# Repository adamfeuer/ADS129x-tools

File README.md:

# DEPRECATED

**This repository is deprecated. All software development on these tools is happening elsewhere.** 

**It is recommended you switch to using the successor projects:**

* [HackEEG Arduino driver software](https://github.com/starcat-io/hackeeg-driver-arduino)
* [HackEEG Python client software](https://github.com/starcat-io/hackeeg-client-python)
* [HackEEG shield hardware design files](https://github.com/starcat-io/hackeeg-shield)
* [HackEEG Rust client software](https://github.com/starcat-io/hackeeg-client-rust)

## ADS129x-tools

This is a collection of software for working with the TI ADS129x series of analog to digital
converter chips.

The [TI ADS1299](http://www.ti.com/product/ads1299) is a 24-bit 8-channel ADC meant specifically for EEG, with 24x programmable gain amplifiers and much of the analog circuitry needed for EEG. It is capable of digitizing 16,000 samples per second at 24 bit resolution. The ADS1299-4 is a 4-channel version of the ADS1299; the ADS1299-6 is a 6-channel version.

The [TI ADS1298](http://www.ti.com/product/ads1298) is a 24-bit, 8-channel ADC chip with SPI interface, and 12x programmable gain amplifiers,
meant for ECG and EEG. The ADS1294 is a 4-channel version; ADS1296 is a 6 channel version. 

The ADS1299 and ADS1298 family of chips are ideally suited for digitizing biological signals.

## Arduino drivers

The ads129x-driver/ directory contains an Arduino sketch and associated C/C++ files that make up a driver for ADS129x chips. So far it has only been tested on the ADS1299 and ADS1298, but should work on the other models. This driver has been tested on the Arduino Due and Mega2560, but should also work on other Arduinos. The DMA mode can only be used on the Arduino Due.

The driver has a text-mode interface, so can be used without any client software – just open up a serial port to the SAM3X8E native USB port (line endings NL+CR). It also has a JSONLines mode for easy parsing by client programs and a MessagePack mode for efficient binary communication. 

In MessagePack mode, using the Arduino Due's native SPI DMA, driver can read from the ADS1299 at 16,000 samples per second, and can send that data on to the host via the Arduino Due's USB 2.0 High Speed connection at the same rate. 

By default the driver uses the Arduino library's software SPI (without DMA), and can read and send 8,000 samples per second in that configuration on the Arduino Due, either in JSON Lines mode or MessagePack mode. Other Arduinos will have lower performance.

When in MessagePack mode, MessagePack format is only used to transfer data in `rdata` and `rdatac` commands; all other communication takes place by JSON Lines.

In text mode, samples are encoded using the [base64](http://en.wikipedia.org/wiki/Base64) encoding by default.

## Installing

You must install the [ArduinoJson](https://arduinojson.org/v6/doc/installation/) library before compiling this driver.

## Using the Driver

The commands that are available are:

* RREG – read register. Takes two hex digits as an argument (one byte, for example: FF). Argument 1 is the register to read.
Returns a single hex-encoded byte (for example, 0E) that represents the contents of the register.
* WREG – write register. Takes two hex-encoded bytes as arguments, separated by a space. Argument 1 is the register to write, argument 2 is the register value.
* RDATA – read one sample of data from the ADS129x chip. Returns 3 bytes of header, plus 3 bytes x number of channels (8 for ADS1298 or ADS1299), encoded using base64 or packed hex in text mode, and JSON Lines byte array, or MessagePack byte array, depending on the protocol
* RDATAC – start read data continuous mode. Data is read into a buffer in the Arduino RAM, and streamed to the client one sample at a time, either in packed base64 format or packed hex format in text, JSON Lines byte array, or MessagePack byte array, depending on the protocol.
* SDATAC – stop read data continuous mode. 
* VERSION – reports the driver version
* SERIALNUMBER – reports the HackEEG serial number (UUID from the onboard 24AA256UID-I/SN I2S EEPROM)
* LEDON – turns on the Arduino Due onboard LED.
* LEDOFF – turns off the Arduino Due onboard LED.
* BOARDLEDON – turns on the HackEEG Shield LED. (HackEEG shield has a blue LED connected to ADS1299 GPIO4) 
* BOARDLEDOFF – turns off the HackEEG Shield LED. 
* BASE64 – RDATA/RDATAC commands will encode data in base64.
* TEXT – communication protocol switches to text. See the Communication Protocol section.
* JSONLINES – communication protocol switches from text to [JSONLines](http://jsonlines.org/). This is a text-oriented serialization format with libraries in many languages. See the Communication Protocol section.
* MESSAGEPACK – communication protocol switches from text to [MessagePack](https://msgpack.org) for `rdatac` data only. This is a concise binary serialization format with libraries in many languages. See the Communication Protocol section.
* HEX – RDATA commands will encode data in hexidecimal format.
* HELP – prints a list of available commands.

## General Operation

The ADS129x chips are configured by reading and writing registers. See the chip datasheet for more information about configuring the ADS129x and reading data from it.

If the host program (the program that reads data from the driver) does not pull data from the serial or USB interface fast enough, the driver will block on sending when the serial or USB buffers fill up. This will cause the driver to lose samples. 

The driver uses the Arduino Native port for serial communication, because it is capable of 2 megabits per second or more.

In most applications, the Python 3 usage will go something like this:

```python
#!/usr/bin/env python

SERIAL_PORT_PATH="/dev/cu.usbmodem14434401"  # your actual path to the Arduino Native serial port device goes here
import sys
import hackeeg
from hackeeg import ads1299

hackeeg = hackeeg.HackEEGBoard(SERIAL_PORT_PATH)
hackeeg.connect()
hackeeg.sdatac()
hackeeg.reset()
hackeeg.blink_board_led()
hackeeg.disable_all_channels()
sample_mode = ads1299.HIGH_RES_250_SPS | ads1299.CONFIG1_const
hackeeg.wreg(ads1299.CONFIG1, sample_mode)
test_signal_mode = ads1299.INT_TEST_4HZ | ads1299.CONFIG2_const
hackeeg.wreg(ads1299.CONFIG2, test_signal_mode)
hackeeg.enable_channel(7)
hackeeg.wreg(ads1299.CH7SET, ads1299.TEST_SIGNAL | ads1299.GAIN_1X)
hackeeg.rreg(ads1299.CH5SET)

# Unipolar mode - setting SRB1 bit sends mid-supply voltage to the N inputs
hackeeg.wreg(ads1299.MISC1, ads1299.SRB1)
# add channels into bias generation
hackeeg.wreg(ads1299.BIAS_SENSP, ads1299.BIAS8P)
hackeeg.rdatac()
hackeeg.start()

while True:
    result = hackeeg.read_response()
    status_code = result.get('STATUS_CODE')
    status_text = result.get('STATUS_TEXT')
    data = result.get(hackeeg.DataKey)
    if data:
        decoded_data = result.get(hackeeg.DecodedDataKey)
        if decoded_data:
            timestamp = decoded_data.get('timestamp')
            ads_gpio = decoded_data.get('ads_gpio')
            loff_statp = decoded_data.get('loff_statp')
            loff_statn = decoded_data.get('loff_statn')
            channel_data = decoded_data.get('channel_data')
            print(f"timestamp:{timestamp} | gpio:{ads_gpio} loff_statp:{loff_statp} loff_statn:{loff_statn} |   ",
                  end='')
            for channel_number, sample in enumerate(channel_data):
                print(f"{channel_number + 1}:{sample} ", end='')
            print()
        else:
            print(data)
        sys.stdout.flush()
```

## SPI DMA 

The driver running on the Arduino communicates with the ADS1299 chip via the SPI interface. For data rates from 250 to 8,192 samples per second, the driver can use the Arduino API's built in software SPI. This is simplest.

To use the 16,384 samples per second data rate, or to reduce CPU load on the Arduino Due, the driver can use the Arduino Due's [Atmel SAM3X8E](https://ww1.microchip.com/downloads/en/DeviceDoc/Atmel-11057-32-bit-Cortex-M3-Microcontroller-SAM3X-SAM3A_Datasheet.pdf) CPU's built-in SPI DMA ([Direct Memory Access](https://en.wikipedia.org/wiki/Direct_memory_access)) controller. Using the SPI DMA offloads all SPI communication to the SAM3X8E DMA controller, freeing up the CPU to do other tasks like serial communication. 

To enable this, change the following constants in `SpiDma.cpp` from this:

Arduino software SPI:

```
#define USE_ARDUINO_SPI_LIBRARY 1
#define USE_NATIVE_SAM3X_SPI 0
```

To this (HackEEG SPI DMA):

```
#define USE_ARDUINO_SPI_LIBRARY 0
#define USE_NATIVE_SAM3X_SPI 1
```

Then recompile and upload the driver sketch to the Arduino.

## Communication Protocol

### Text mode

The driver starts up in this mode. This mode is easiest to use when quick communication with the board is needed without a client program. 

When the command TEXT is given, the driver communication protocol switches to text, and the response will be in text format. Commands can be given in lower or upper case, parameters separated by a space. Responses are given on one line, starting with a status code (200 for OK, errors are in the 300s and 400s.) Commands can be given in upper or lower case.

### JSON Lines mode

Give the JSONLINES command to switch to this mode.

When the command JSONLINES is given, the driver communication protocol switches to [JSON Lines](http://jsonlines.org/) format, and the response will be in JSON Lines format. Commands and Responses are a single map, with keys and values determine the command and parameters. The format is as follows (on separate lines for readability; in use, the entire JSON blob would be on its own line):

#### Commands:

```
{
    COMMAND: "<command-name>",
    PARAMETERS: [ <param1>, <param2>, ... ]
}
```

#### Responses:

```
{
    STATUS_CODE: <status-code>,
    STATUS_TEXT: "<status-text>",
    HEADERS: ["header1", "header2", ... ],
    DATA: [value1, value2, value3, ... ]
}
```

Here is an example exchange:

```
{"COMMAND" : "boardledon"}
{"STATUS_CODE" : 200, "STATUS_TEXT": "Ok" }

```

Headers are optional and may or may not be provided.

#### JSON Lines concise mode for `rdata` and `rdatc` responses

For `rdata` and `rdatac` responses, in order to send data at high speeds, a special response format is used that is similar to the MessagePack format:

```
{
    C: <status-code>,
    D: "<base64-encoded byte-array>"
}
```

In concise JSON Lines mode, status text is omitted. The data is sent as a base64-encoded byte array to minimize transformation of the data into human-readable form. This allows faster transfer. See below for the format of the decoded data byte-array.

#### Software library

The Arduino driver uses the [ArduinoJson](https://arduinojson.org/) library for encoding and decoding JSON Lines data, except for `rdata` and `rdatac` messages– those use a custom, optimized sending routine.

### MessagePack mode

Give the MESSAGEPACK command to switch to this mode.

When the command MESSAGEPACK is given, the driver communication protocol for `rdata` and `rdatac` data packets ONLY switches to [MessagePack](https://msgpack.org) concise binary format. Commands are still given in JSON Lines format, and responses for all commands other than `rdata` and `rdatac` will be in JSON Lines. Responses for `rdata` and `rdatac` will be in MessagePack format. This mode is available to improve data transfer speed since the binary data from the SPI interface can be transferred as-is with no copying or transformation.

The format is as follows (on separate lines as JSON for readability, in use this would be packed as a binary structure):

#### Responses:

```
{
    C: <status-code>,
    D: <byte-array>
}
```

In MessagePack mode, status text is omitted.

#### Software library

The Arduino driver uses the [ArduinoJson](https://arduinojson.org/) library for encoding and decoding MessagePack data, except for `rdata` and `rdatac` messages– those use a custom, optimized sending routine.

### Byte-array Format

The packed byte-array used for `rdata` and `rdatac` transfers has this format:

| position | function      | byte |
|----------|---------------|------|
| 00       | timestamp     |    0 |
| 01       | timestamp     |    1 |
| 02       | timestamp     |    2 |
| 03       | timestamp     |    3 |
| 04       | sample number |    0 |
| 05       | sample number |    1 |
| 06       | sample number |    2 |
| 07       | sample number |    3 |
| 08       | channel 1     |    0 |
| 09       | channel 1     |    1 |
| 10       | channel 1     |    2 |
| 11       | channel 2     |    0 |
| 12       | channel 2     |    1 |
| 13       | channel 2     |    2 |
| 14       | channel 3     |    0 |
| 15       | channel 3     |    1 |
| 16       | channel 3     |    2 |
| 17       | channel 4     |    0 |
| 18       | channel 4     |    1 |
| 19       | channel 4     |    2 |
| 20       | channel 5     |    0 |
| 21       | channel 5     |    1 |
| 22       | channel 5     |    2 |
| 23       | channel 6     |    0 |
| 24       | channel 6     |    1 |
| 25       | channel 6     |    2 |
| 26       | channel 7     |    0 |
| 27       | channel 7     |    1 |
| 28       | channel 7     |    2 |
| 29       | channel 8     |    0 |
| 30       | channel 8     |    1 |
| 31       | channel 8     |    2 |

* `timestamp` is an unsigned long, the result of calling the Arduino's `micros()` function right before the sample is taken.
* `sample number` is an unsigned long, the value is incremented for every sample received by the driver. It is reset every time you issue the `start` command. You can analyze the sample number sequence on the client to see if your client code is dropping or missing samples.
* For an example Python decoding function, see [`_decode_data()`](https://github.com/adamfeuer/ADS129x-tools/blob/master/ads129x_client/hackeeg/driver.py#L123-L152) in the file `hackeeg/driver.py`.

## Python Client Software

The Python client software is designed to run on a laptop computer. There is a `hackeeg` driver Python module for communicating with the Arduino over the USB serial port, a command line client (`hackeeg_shell` wrapper and `hackeeg_shell.py` Python client), and a demonstration and performance testing script (`hackeeg_test.py`). 

The `hackeeg_shell.py` and `hackeeg_test.py` programs set the Arduino driver to JSON Lines mode, and communicate with it that way. They issue JSON Lines commands to the Arduino, and recieve JSON Lines or MessagePack data in response.

Using Python 3.6.5 on a 2017 Retina Macbook Pro, connected to an Arduino Due configured to use the SPI DMA included in the driver, and using the MessagePack mode, the `hackeeg_test.py` program can read and transfer 8 channels of 24-bit resolution data at 16,384 samples per second, the maximum rate of the ADS1299 chip.

The Python client software requires the [PySerial](https://github.com/pyserial/pyserial) module.

## Hardware

If you are looking for a full Arduino shield with analog input capability, you might
be interested in the [HackEEG Shield](https://github.com/adamfeuer/hackeeg-shield).
The HackEEG shield is designed for use with the ADS1299.

For prototyping software, the [ADS1298 breakout board](https://github.com/adamfeuer/ADS1298-breakout) might be useful. It is designed for the ADS1298, but should also work with the ADS1294, ADS1296, or ADS1299.

## Credits

This software would not be possible without the help of many people:

* Kendrick Shaw, Ace Medlock, and Eric Herman (parts of the ADS129x.h header file and some parts of the ADS129x driver, see [OpenHardwareExG project](https://github.com/OpenElectronicsLab/OpenHardwareExG) for more info.
* Chris Rorden (some parts of the ADS1298 driver)
* Stefan Rado (SerialCommand library)
* Steven Cogswell (SerialCommand library)
* William Greiman (SPI DMA library)
* Cristian Maglie (SPI DMA library)
* Bill Porter (SPI DMA library)
* Adam Rudd ([Base64](https://github.com/adamvr/arduino-base64) library)
* Benoît Blanchon ([ArduinoJson](https://arduinojson.org/) library)

If I forgot to credit you, please let me know!

If you have questions, comments, or improvements, I would love to know them! Pull requests welcome!

cheers <br/>
adam <br/>
<br/>
Adam Feuer <br/>
adam@starcat.io<br/>
[Starcat LLC](https://starcat.io)<br/>
Seattle, WA, USA <br/>

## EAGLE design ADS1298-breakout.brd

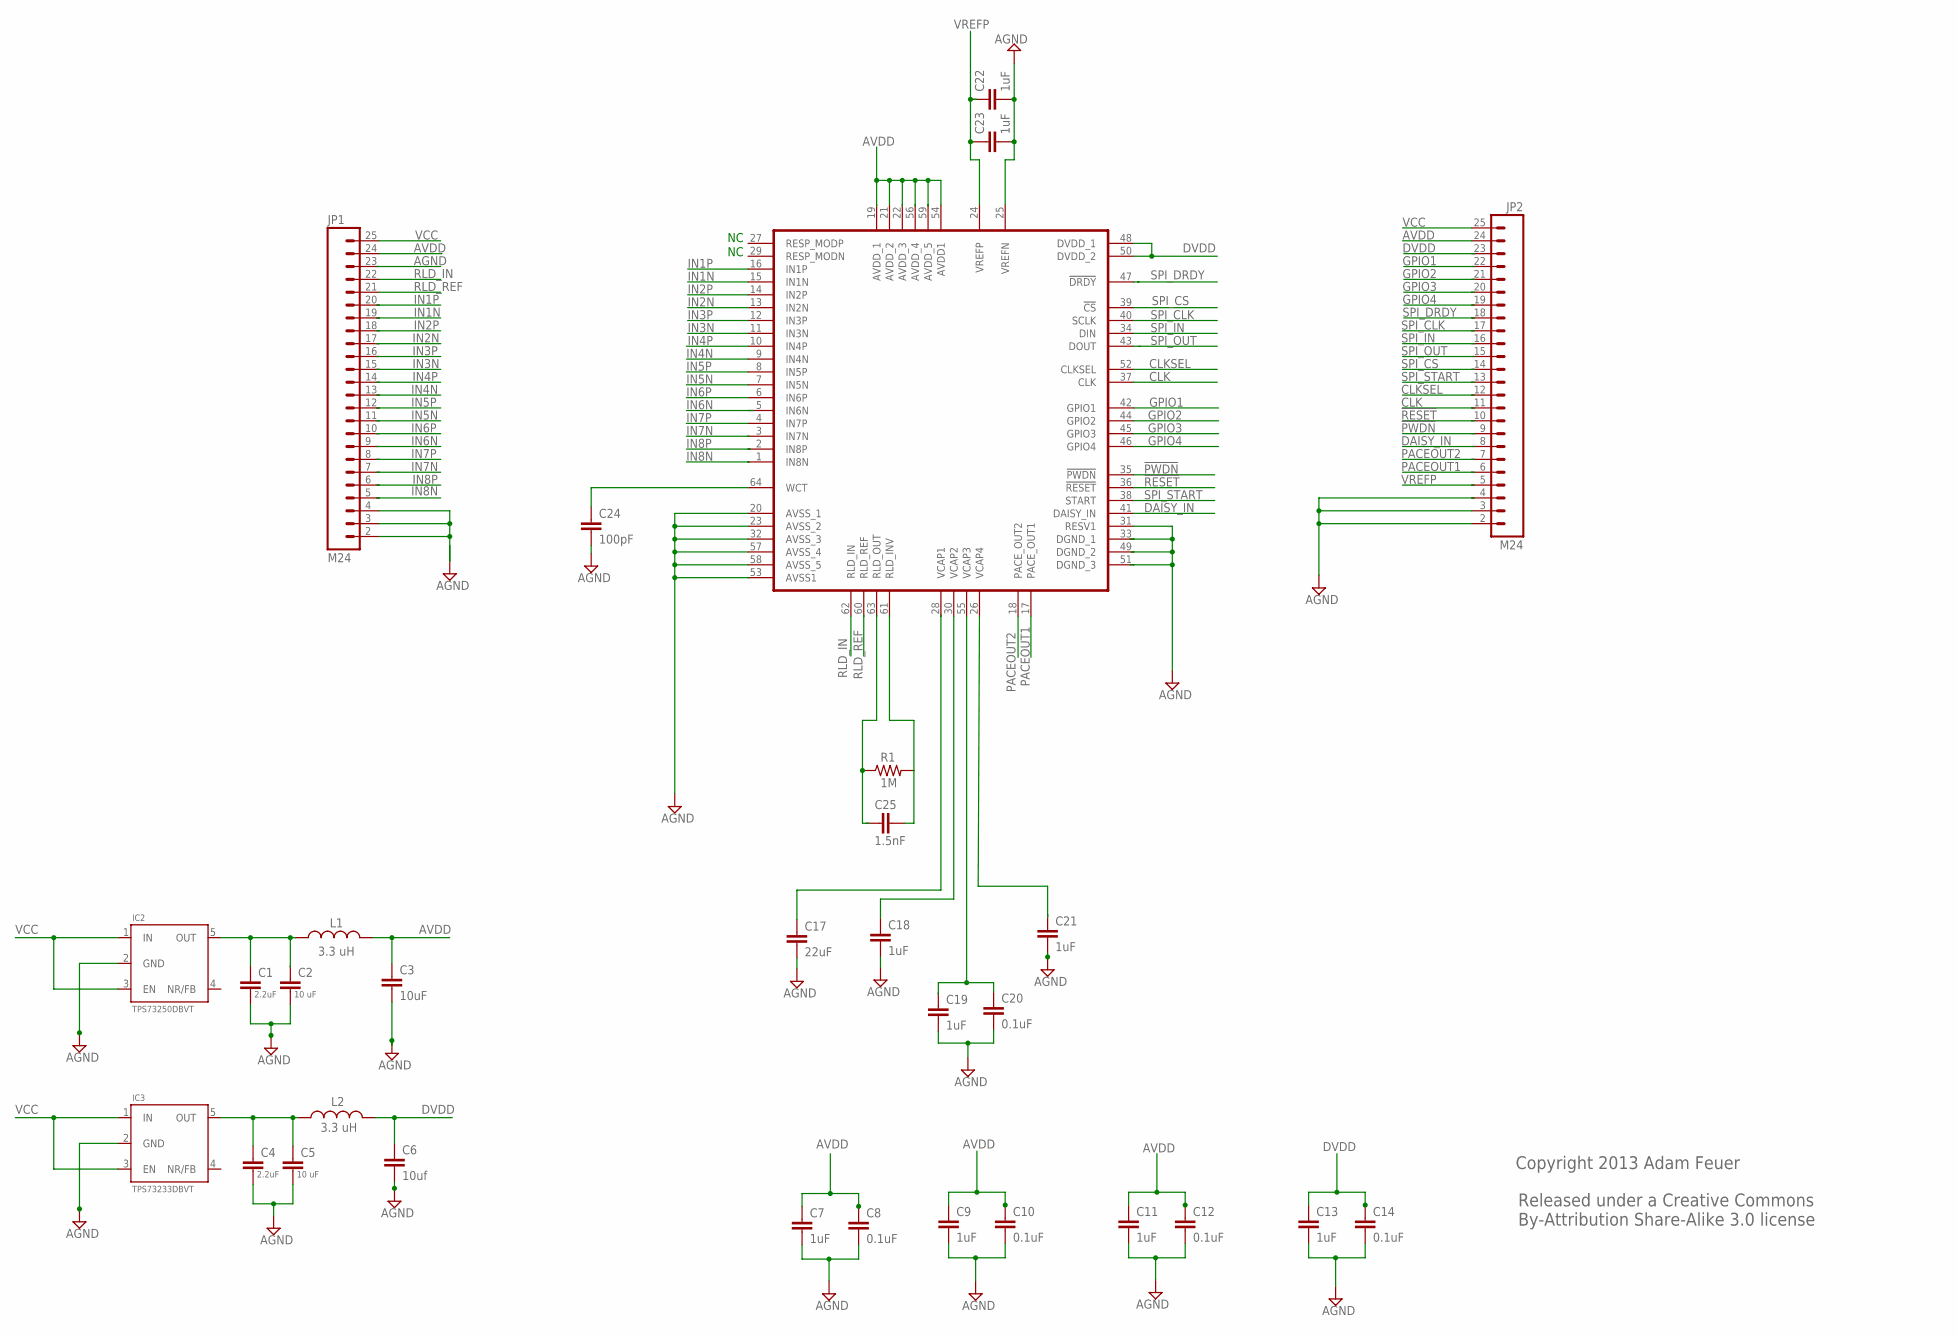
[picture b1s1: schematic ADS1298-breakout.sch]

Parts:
C1, C4: 2.2uF; 0603-CAP
C2, C5: 10 uF; 0603-CAP
C3: 10uF; 0603-CAP
C6: 10uf; 0603-CAP
C7, C9, C11, C13, C18, C19, C21, C22, C23: 1uF; 0603-CAP
C8, C10, C12, C14, C20: 0.1uF; 0603-CAP
C17: 22uF; 0603-CAP
C24: 100pF; 0603-CAP
C25: 1.5nF; 0603-CAP
IC1: ADS1298*PAG*; TQFP64
IC2: TPS73250DBVT; SOT23-5
IC3: TPS73233DBVT; SOT23-5
JP1, JP2: M24; 1X24
L1, L2: 3.3 uH; 0603
R1: 1M; 0603-RES

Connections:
!PWDN: IC1.35 (!PWDN), JP2.9
!RESET: IC1.36 (!RESET), JP2.10
AGND: C1.2, C2.2, C3.2, C4.2, C5.2, C6.2, C7.2, C8.2, C9.2, C10.2, C11.2, C12.2, C13.2, C14.2, C17.2, C18.2, C19.2, C20.2, C21.2, C22.2, C23.2, C24.2, IC1.20 (AVSS_1), IC1.23 (AVSS_2), IC1.25 (VREFN), IC1.31 (RESV1), IC1.32 (AVSS_3), IC1.33 (DGND_1), IC1.49 (DGND_2), IC1.51 (DGND_3), IC1.53 (AVSS1), IC1.57 (AVSS_4), IC1.58 (AVSS_5), IC2.2 (GND), IC3.2 (GND), JP1.2, JP1.3, JP1.4, JP1.23, JP2.2, JP2.3, JP2.4
AVDD: C3.1, C7.1, C8.1, C9.1, C10.1, C11.1, C12.1, IC1.19 (AVDD_1), IC1.21 (AVDD_2), IC1.22 (AVDD_3), IC1.54 (AVDD1), IC1.56 (AVDD_4), IC1.59 (AVDD_5), JP1.24, JP2.24, L1.2
CLK: IC1.37 (CLK), JP2.11
CLKSEL: IC1.52 (CLKSEL), JP2.12
DAISY_IN: IC1.41 (DAISY_IN), JP2.8
DVDD: C6.1, C13.1, C14.1, IC1.48 (DVDD_1), IC1.50 (DVDD_2), JP2.23, L2.2
GPIO1: IC1.42 (GPIO1), JP2.22
GPIO2: IC1.44 (GPIO2), JP2.21
GPIO3: IC1.45 (GPIO3), JP2.20
GPIO4: IC1.46 (GPIO4), JP2.19
IN1N: IC1.15 (IN1N), JP1.19
IN1P: IC1.16 (IN1P), JP1.20
IN2N: IC1.13 (IN2N), JP1.17
IN2P: IC1.14 (IN2P), JP1.18
IN3N: IC1.11 (IN3N), JP1.15
IN3P: IC1.12 (IN3P), JP1.16
IN4N: IC1.9 (IN4N), JP1.13
IN4P: IC1.10 (IN4P), JP1.14
IN5N: IC1.7 (IN5N), JP1.11
IN5P: IC1.8 (IN5P), JP1.12
IN6N: IC1.5 (IN6N), JP1.9
IN6P: IC1.6 (IN6P), JP1.10
IN7N: IC1.3 (IN7N), JP1.7
IN7P: IC1.4 (IN7P), JP1.8
IN8N: IC1.1 (IN8N), JP1.5
IN8P: IC1.2 (IN8P), JP1.6
unnamed: C4.1, C5.1, IC3.5 (OUT), L2.1
unnamed: C1.1, C2.1, IC2.5 (OUT), L1.1
unnamed: C17.1, IC1.28 (VCAP1)
unnamed: C18.1, IC1.30 (VCAP2)
unnamed: C19.1, C20.1, IC1.55 (VCAP3)
unnamed: C24.1, IC1.64 (WCT)
unnamed: C21.1, IC1.26 (VCAP4)
PACEOUT1: IC1.17 (PACE_OUT1), JP2.6
PACEOUT2: IC1.18 (PACE_OUT2), JP2.7
RLD_IN: IC1.62 (RLD_IN), JP1.22
RLD_INV: C25.2, IC1.61 (RLD_INV), R1.2
RLD_OUT: C25.1, IC1.63 (RLD_OUT), R1.1
RLD_REF: IC1.60 (RLD_REF), JP1.21
SPI_CLK: IC1.40 (SCLK), JP2.17
SPI_CS: IC1.39 (!CS), JP2.14
SPI_DRDY: IC1.47 (!DRDY), JP2.18
SPI_IN: IC1.34 (DIN), JP2.16
SPI_OUT: IC1.43 (DOUT), JP2.15
SPI_START: IC1.38 (START), JP2.13
VCC: IC2.1 (IN), IC2.3 (EN), IC3.1 (IN), IC3.3 (EN), JP1.25, JP2.25
VREFP: C22.1, C23.1, IC1.24 (VREFP), JP2.5

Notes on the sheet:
Released under a Creative Commons By-Attribution Share-Alike 3.0 license
Copyright 2013 Adam Feuer

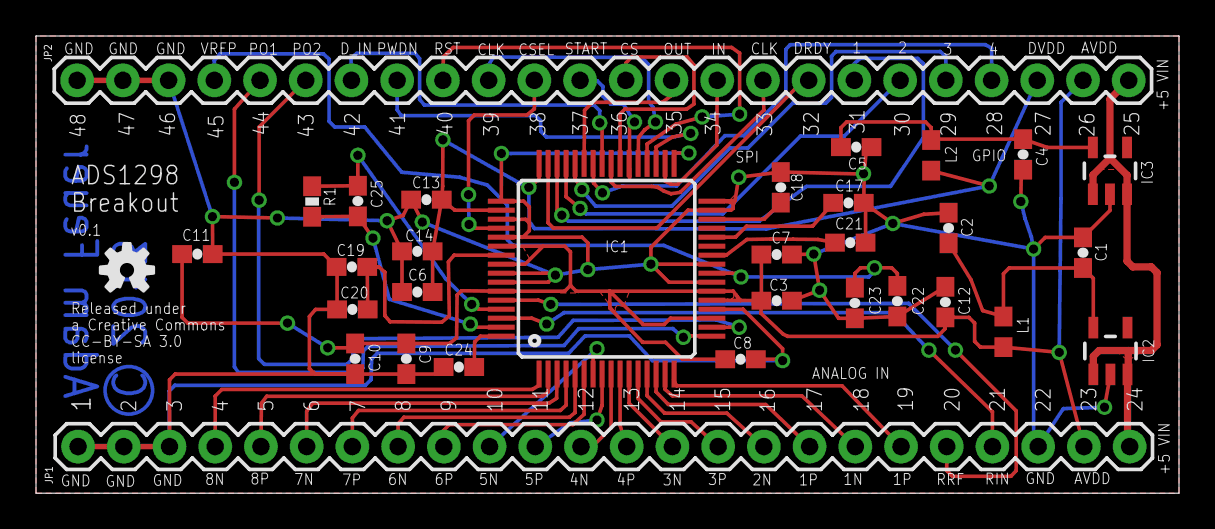
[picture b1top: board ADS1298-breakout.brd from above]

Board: 2 copper layers, 63.5 x 25.4 mm, 32 parts (0 on the bottom side), 49 nets.

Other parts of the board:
U$1: OSHW-LOGO-S

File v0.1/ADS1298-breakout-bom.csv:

"Part";"Value";"Device";"Package";"Description";"";
"C1";"2.2uF";"CAP0603-CAP";"0603-CAP";"Capacitor";"";
"C2";"10 uF";"CAP0603-CAP";"0603-CAP";"Capacitor";"";
"C3";"10uF";"CAP0603-CAP";"0603-CAP";"Capacitor";"";
"C4";"2.2uF";"CAP0603-CAP";"0603-CAP";"Capacitor";"";
"C5";"10 uF";"CAP0603-CAP";"0603-CAP";"Capacitor";"";
"C6";"10uf";"CAP0603-CAP";"0603-CAP";"Capacitor";"";
"C7";"1uF";"CAP0603-CAP";"0603-CAP";"Capacitor";"";
"C8";"0.1uF";"CAP0603-CAP";"0603-CAP";"Capacitor";"";
"C9";"1uF";"CAP0603-CAP";"0603-CAP";"Capacitor";"";
"C10";"0.1uF";"CAP0603-CAP";"0603-CAP";"Capacitor";"";
"C11";"1uF";"CAP0603-CAP";"0603-CAP";"Capacitor";"";
"C12";"0.1uF";"CAP0603-CAP";"0603-CAP";"Capacitor";"";
"C13";"1uF";"CAP0603-CAP";"0603-CAP";"Capacitor";"";
"C14";"0.1uF";"CAP0603-CAP";"0603-CAP";"Capacitor";"";
"C17";"22uF";"CAP0603-CAP";"0603-CAP";"Capacitor";"";
"C18";"1uF";"CAP0603-CAP";"0603-CAP";"Capacitor";"";
"C19";"1uF";"CAP0603-CAP";"0603-CAP";"Capacitor";"";
"C20";"0.1uF";"CAP0603-CAP";"0603-CAP";"Capacitor";"";
"C21";"1uF";"CAP0603-CAP";"0603-CAP";"Capacitor";"";
"C22";"1uF";"CAP0603-CAP";"0603-CAP";"Capacitor";"";
"C23";"1uF";"CAP0603-CAP";"0603-CAP";"Capacitor";"";
"C24";"100pF";"CAP0603-CAP";"0603-CAP";"Capacitor";"";
"C25";"1.5nF";"CAP0603-CAP";"0603-CAP";"Capacitor";"";
"IC1";"ADS1298*PAG*";"ADS1298*PAG*";"TQFP64";"8-Channel, 24-Bit Analog-To-Digital Converter With Integrated ECG Front End.";"";
"IC2";"TPS73250DBVT";"TPS732XXDBV";"SOT23-5";"Cap-Free, NMOS, 250mA Low Dropout Regulator";"";
"IC3";"TPS73233DBVT";"TPS732XXDBV";"SOT23-5";"Cap-Free, NMOS, 250mA Low Dropout Regulator";"";
"JP1";"M24";"M24";"1X24";"1x24 .1" header";"";
"JP2";"M24";"M24";"1X24";"1x24 .1" header";"";
"L1";"3.3 uH";"INDUCTOR0603";"0603";"Inductors";"";
"L2";"3.3 uH";"INDUCTOR0603";"0603";"Inductors";"";
"R1";"1M";"RESISTOR0603-RES";"0603-RES";"Resistor";"";

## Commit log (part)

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2013-09-06 initial addition - first schematic draft done
2013-09-06 added cc-by-sa 3.0 license file; and updated readme
2013-09-06 minor readme mods
2013-09-06 added PDF schematic
2013-09-06 added note about being untested
2013-09-06 minor update to readme
2013-09-06 schematic passes ERC
2013-09-06 updated PDF schematic with latest schematic
2013-09-07 changed pinout to facilate routing; board is still unrouted
2013-09-10 corrected minor errors in schematic; changed from 20 to 24 pin headers; board partially routed
2013-09-10 fixed pin spacing so it is 0.1 inch; fixed board outline so it is even on all edges
2013-09-10 added OSH Park design rules
2013-09-10 partially routed board passes design rule check; analog ins, GPIOs, and a few other signals still need routing
2013-09-11 board completely routed, passes design rule check
2013-09-11 changed drill holes to be 0.038 inch, compatible with AP Circuits
2013-09-11 changed via drill holes to be 0.020 inch, compatible with AP Circuits
2013-09-11 added packaging scripts
2013-09-11 added OSH Park cam job
2013-09-12 top silkscreen has pin numbers and functions; board name and version; OSH logo; and CC-BY-SA license
2013-09-12 renamed package-advanced-circuits to package-generic.sh
2013-09-12 changed advanced circuits to cam in script
2013-09-12 added AP Circuits design rules
2013-09-12 minor cosmetic updates to silkscreen
2013-09-12 added eagle project (pro) file
2013-09-12 reorganizing files
2013-09-12 added cam and dru files
2013-09-12 moved cam and dru files to cam directory
2013-10-14 updating docs with how to wire instructions; Arduino DUE pinout; photos; and updated PDF and BOM files
2013-10-14 added pin label to README wiring table
2013-10-14 added URL for Chris Rorden's Neuropsychology Lab to README
2013-10-14 formatting fix for section header; added remark about v0.1 being tested.
2013-10-14 renamed sketch to make Arduino IDE happy
2013-10-23 added ads1298_driver files - initial add
2013-10-23 rreg and wreg can parse register and values in hex now
2013-10-23 ads1298_driver can now read registers
2013-10-24 ads1298_driver can now write registers
2013-10-24 ads1298_driver can now send samples continuously (RDATAC) and stop sending (SDATAC)
2013-10-24 rdata command works; some code cleanup
2013-10-24 minor optimizations - can now reach about 2200 samples per second
2013-10-25 minor performance optimization - still around 2k SPS
2013-10-25 minor optimizations - with pypy it does about 10k sps
2013-10-25 can do 8k samples per second using pypy
2013-10-25 changed SPI CS from pin 53 to pin 52 to match SAM3X8E CS2 pin
2013-10-25 adding needed Base64 library - forgot to add it in last commit
2013-10-26 adding SpiDma library files that I forgot to add earlier - needed for the 16k samples per second driver
2013-10-27 splitting out ADS1298 driver software into a separate repo
2013-10-27 fixed formatting problem with contributors
2013-10-27 fixed another formatting problem with the list of driver commands
2013-10-27 added info on the python scripts; added link to TI ADS1299 page
2013-11-01 updates to SpiDma driver to support SPI_MODE0 and LSBFIRST
2013-11-01 code cleanup (variable names); added help command; added hex and base64 modes
2013-11-01 updated license headers in all code files
2013-11-01 updated receive test script to base64 decode some of the data; now leaves driver in a known good state so the script can be run repeatedly
2013-11-03 added ifndef guard to SerialCommand.h
2013-11-03 added go test programs
2013-11-03 updates to make chunked reader more reliable - leaves driver in good state
2013-11-03 added base64 decoder as post processing step
2013-11-06 go client now uses buffered pipe instead of byte buffer - much faster
2014-01-03 renamed ads1298_driver to ads129x_driver
2014-01-08 renamed ads1298 files to ads129x
2014-01-08 added boardledon and boardledoff commands
2014-01-17 HackEEG board working in Arduino SPI and SAM3X native SPI DMA modes; added status command; add placeholder serialnumber command
2014-01-17 added function_generator sketch for use as a test system
2014-01-17 version command now reports board name, maker, driver version, hardware type, max channels, active channels; changed namespace to ADS129x
2014-01-18 added blank line to the end of every command, to delineate end of output; added status text to start, stop, standby, wakeup, and reset commands
2014-09-13 fixed typo in chip number
2014-09-13 updated readme for BOARDLEDON/OFF commands
2014-10-28 added Hardware section to README
    - with links to HackEEG and ADS1298 repos
2014-10-28 fixing typo in README
2016-02-04 disabling SPI DMA library - use Arduino SPI
2016-02-04 commenting out ADS1299 setup temporarily
    - also disabled Serial1 logging
2016-06-04 uncommenting ads_setup
2016-06-04 initial addition of hackeeg commandline client
2016-06-04 added numpy to requirements.txt
2016-06-04 added gitignore
2016-06-05 updated signature
2019-07-04 formatting and credits
2019-07-04 copyright header
2019-07-04 work in progress - formatting, new commands stubbed out, copyright
2019-07-05 update readme with sample rate and ADS129x chip info
2019-07-05 added hackeeg_demo.py as copy of hackeeg_commandline.py
    - so we can use both while the CLI is being transformed
2019-07-05 autopep8 format
2019-07-05 create _serialWrite method and have all commands use it
2019-07-05 optimize imports
2019-07-06 JSONLines communication protocol conversion - work in progress
    - untested, client not updated yet
2019-07-09 work in progress - converted client to JSONLines
    - haven't tested with driver yet
2019-07-17 work in progress on Python JSONLines driver
2019-07-17 added pyenv python-version file
2019-07-22 Serial port debugging working
2019-07-23 better error handling on json parse failure
2019-09-03 parameterize commands; jsonlines working
    - also micros() now correctly uses unsigned long
2019-09-04 python jsonlines client working for micros, nop, boardled on/off
    - TODO: read and write registers, read data, messagepack
2019-09-04 jsonlines client working
2019-09-04 added stubs for all hackeeg driver commands
2019-09-04 renamed hackeeg_json_commandline to hackeeg_shell
2019-09-05 implemented status command for jsonlines; some refactoring
2019-09-06 rreg working in decimal mode
    - TODO:
    - wreg
    - hex display mode for client
2019-09-06 initial addition of wrapper script
2019-09-11 numerical output now in hexidecimal by default; mode on and off switch
2019-09-12 refactoring names to match coding convention
2019-09-12 fixed copyright headers
2019-09-13 refactoring, cleaning up comments
2019-09-17 implemented jsonlines rdatac, start, stop commmands; shell does setup
    - aslo fixed bug reading driver error codes
2019-09-17 fix startup connection problem
2019-09-17 implmented rdatac, sdatac, and stop in client
2019-09-18 rdata working in jsonlines mode
2019-09-18 updated gitignore for .idea, .bin, .elf
2019-09-18 renamed buffers for more clarity
2019-09-18 send_samples working again
2019-09-19 enable and disable all channels convenience method in shell client
2019-09-19 fix shell client command line args
2019-09-19 fixed sdatac response - sends json or text
2019-09-19 sdatac on driver startup
2019-09-19 hackeeg_test now decodes samples correctly
2019-09-19 removing unneeded commented out line
2019-09-19 moved sample decoding to driver
2019-09-19 updated docstring
2019-09-19 minor doc updates, removed un-implemented messagepack docs
    - will add back later in the MessagePack PR
2019-09-19 optimize imports, fix missing import for JSONDecodeError
2019-09-20 removed old erroneous instruction about RingBuffer library
2019-09-20 added example communication exchange
    - and clarified credits
2019-09-20 doc cleanup
2019-09-20 updated example code
2019-09-20 formatting for markdown
2019-09-20 linked base64 library github URL in docs
2019-09-20 c code reformatting
2019-09-20 header file cleanup
2019-09-20 fix gain settings for ADS1299
    - leave ADS1298 settings prefixed by ADS1298_
2019-09-20 header file comment clarification
2019-09-20 update python-related part of readme
2019-10-02 Added MessagePack documentation.
2019-10-02 work in progress on MessagePack protocol
2019-10-04 WIP on jsonlines concise
2019-10-04 removing now-unused hackeeg_demo.py
2019-10-04 MessagePack mode for rdatac working
    - MessagePack mode is just like JSON Lines mode for all commands other
    than rdatac
    - In MessagePack mode, rdata sends its data in in MessagePack format
    - hackeeg_shell.py, hackeeg_test.py, and example.py are updated
    - docs are updated
    - you now have to use the python driver's hackeeg.connect() method to
2019-10-04 better startup error handling for MessagePack rdatac mode
2019-10-08 fix naming error from bad merge
2019-10-08 naming convention changes for function names
2019-10-09 unpack concise JSON
2019-10-10 pass debug flag -d (and all other params)
2019-10-10 use universal newline mode and io module for buffered stream
    - to prevent errors
2019-10-10 work in progress – can now read 16k SPS with one channel
2019-10-10 cleanup; fixed extra send of fake data, now just below 16k SPS
2019-10-10 added hackeeg_test_speed wrapper script
2019-10-10 messagepack protocol working at 8K SPS setting
    - at 16K SPS setting, can only read about 10K SPS
2019-10-10 with SPI DMA, jsonlines working at 8k SPS; messagepack at 16k SPS
2019-10-10 more friendly commandline arguments; code cleanup
2019-10-10 combined hackeeg_test.py and hackeeg_test_speed.py for simplicity
    - quiet option now does performance test
2019-10-10 added hackeeg_test wrapper script
2019-10-10 remove unneeded sync command
2019-10-10 updated docs to reflect new performance tests
2019-10-10 removed more dead code
2019-10-10 documentation updates for concise JSON protocol used in rdatac mode
2019-10-11 documentation on how to use SPI DMA
2019-10-11 rdata and rdatac documentation fixes
2019-10-11 adds function to smoothly stop data transmission while MessagePack mode–
    - mostly avoids exceptions and other hiccups
    - refactor, moved from hackeeg_test.py
2019-10-11 work in progress on sample number - not working
2019-10-11 use sample number to find dropped samples
2019-10-11 code cleanup
2019-10-11 added sample number to byte array table; added some descriptions
    - of timestamp and sample number
    - linked to python decoding function
2019-10-17 add basic lsl support to hackeeg_test.py
    - creates stream and writes to it if command line options are given
2019-10-17 simple LSL receive data commandline client
    - from the PyLSL examples
2019-10-17 added option to read samples until return key is pressed
2019-10-17 made this script executable
2019-10-18 refactoring for clarity
2019-10-31 fix debugging output
2019-10-31 driver debugging output - work in progress
2019-10-31 streamlining test startup
2019-10-31 python driver debugging output
2019-11-01 updates to get ADC output working (matches ancient code)
    - restoring mistakenly deleted ADS1299 config code
2019-11-05 use IRQ on falling edge instead of polling
2019-11-05 cleanup mistaken SerialUSB to WiredSerial
2019-11-05 add --messagepack commandline option
    - and --hex option for debugging
2019-11-05 code cleanup and update copyright years
2019-11-12 fixing JSONCOMMAND_DEBUG code blocks
2019-11-12 command response cleanup; adsSetup() now done in reset too
2019-11-12 better arduino port detection
2019-11-12 remove commented-out code
2019-11-25 set up HackEEG for human EEG readings on all channels
2019-11-25 added some explanatory comments about SRB1
2019-12-14 removed unneeded commented out line
2019-12-14 renamed hackeeg_test to hackeeg_stream
2019-12-26 Add Python common ignore list
2019-12-28 removing spurious #endif
2019-12-31 added deprecation notice
2019-12-31 added additional deprecation warnings
2019-12-31 fixed deprecation headers
2019-12-31 fix deprecation headers

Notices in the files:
parts and their libraries:
SparkFun-Passives: Licensing: CC v3.0 Share-Alike You are welcome to use this library for commercial purposes.
